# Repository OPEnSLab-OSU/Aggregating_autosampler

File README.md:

# Aggregating_autosampler
Compositing autosampler using weight based sampling targeted for sewage sampling in manholes. Code originally housed in ADS1232 branch of [SingleSampler repository](https://github.com/OPEnSLab-OSU/SingleSampler) and created using [Kawin Pechetratanapanit's sampler framework](https://github.com/OPEnSLab-OSU/OPEnSamplerFramework).

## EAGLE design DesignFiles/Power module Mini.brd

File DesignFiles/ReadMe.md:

[Bill of Materials](https://docs.google.com/spreadsheets/d/12LoKV3FAbf4hfWeB7zsqfaazoJ8oWiLxr8qu5_F6xMY/edit?usp=sharing)

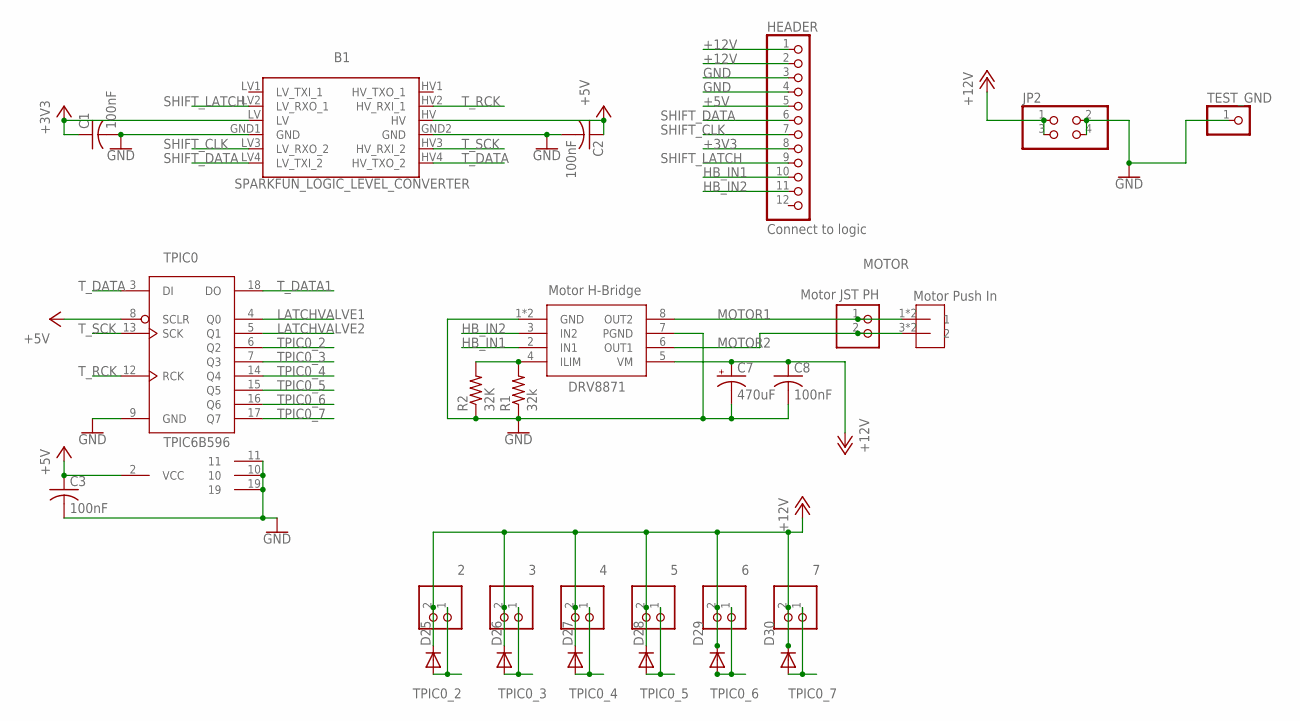
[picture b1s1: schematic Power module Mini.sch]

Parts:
2, 3, 4, 5, 6, 7: 2.5MM_JST_UP_2POS; JST_2POS_2.5MM_UP
B1: SPARKFUN_LOGIC_LEVEL_CONVERTER
C1, C2, C3, C8: 100nF; C1206
C7: 470uF; 140CLH-0810
D25, D26, D27, D28, D29, D30: DIODESOD-123; SOD-123
DRV8871: Motor H-Bridge; SOP8
HEADER: Connect to logic; 1X12
JP2: PINHD-2X2; 2X02
MOTOR: Motor JST PH; JST_2POS_2.5MM_UP
R1: 32k; 0204/5
R2: 32K; R0805
TEST_GND: PINHD-1X1; 1X01
TPIC0: TPIC6B596; DIP20
U$1: Motor Push In; 3.5MM_DIP2

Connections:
+3V3: B1.LV, C1.1, HEADER.8
+5V: B1.HV, C2.1, C3.1, HEADER.5, TPIC0.2 (VCC), TPIC0.8 (SCLR)
+12V: 2.2, 3.2, 4.2, 5.2, 6.2, 7.2, C7.+, C8.1, D25.C, D26.C, D27.C, D28.C, D29.C, D30.C, DRV8871.5 (VM), HEADER.1, HEADER.2, JP2.1, JP2.3
GND: B1.GND1 (GND), B1.GND2 (GND), C1.2, C2.2, C3.2, C7.-, C8.2, DRV8871.1 (GND), DRV8871.7 (PGND), DRV8871.GND, HEADER.3, HEADER.4, JP2.2, JP2.4, R1.1, R2.1, TEST_GND.1, TPIC0.9 (GND), TPIC0.10, TPIC0.11, TPIC0.19
HB_IN1: DRV8871.2 (IN1), HEADER.10
HB_IN2: DRV8871.3 (IN2), HEADER.11
LATCHVALVE1: TPIC0.4 (Q0)
LATCHVALVE2: TPIC0.5 (Q1)
MOTOR1: DRV8871.8 (OUT2), MOTOR.1, U$1.1, U$1.2 (1)
MOTOR2: DRV8871.6 (OUT1), MOTOR.2, U$1.3 (2), U$1.4 (2)
unnamed: DRV8871.4 (ILIM), R1.2, R2.2
SHIFT_CLK: B1.LV3 (LV_RXO_2), HEADER.7
SHIFT_DATA: B1.LV4 (LV_TXI_2), HEADER.6
SHIFT_LATCH: B1.LV2 (LV_RXO_1), HEADER.9
TPIC0_2: 2.1, D25.A, TPIC0.6 (Q2)
TPIC0_3: 3.1, D26.A, TPIC0.7 (Q3)
TPIC0_4: 4.1, D27.A, TPIC0.14 (Q4)
TPIC0_5: 5.1, D28.A, TPIC0.15 (Q5)
TPIC0_6: 6.1, D29.A, TPIC0.16 (Q6)
TPIC0_7: 7.1, D30.A, TPIC0.17 (Q7)
T_DATA: B1.HV4 (HV_TXO_2), TPIC0.3 (DI)
T_DATA1: TPIC0.18 (DO)
T_RCK: B1.HV2 (HV_RXI_1), TPIC0.12 (RCK)
T_SCK: B1.HV3 (HV_RXI_2), TPIC0.13 (SCK)

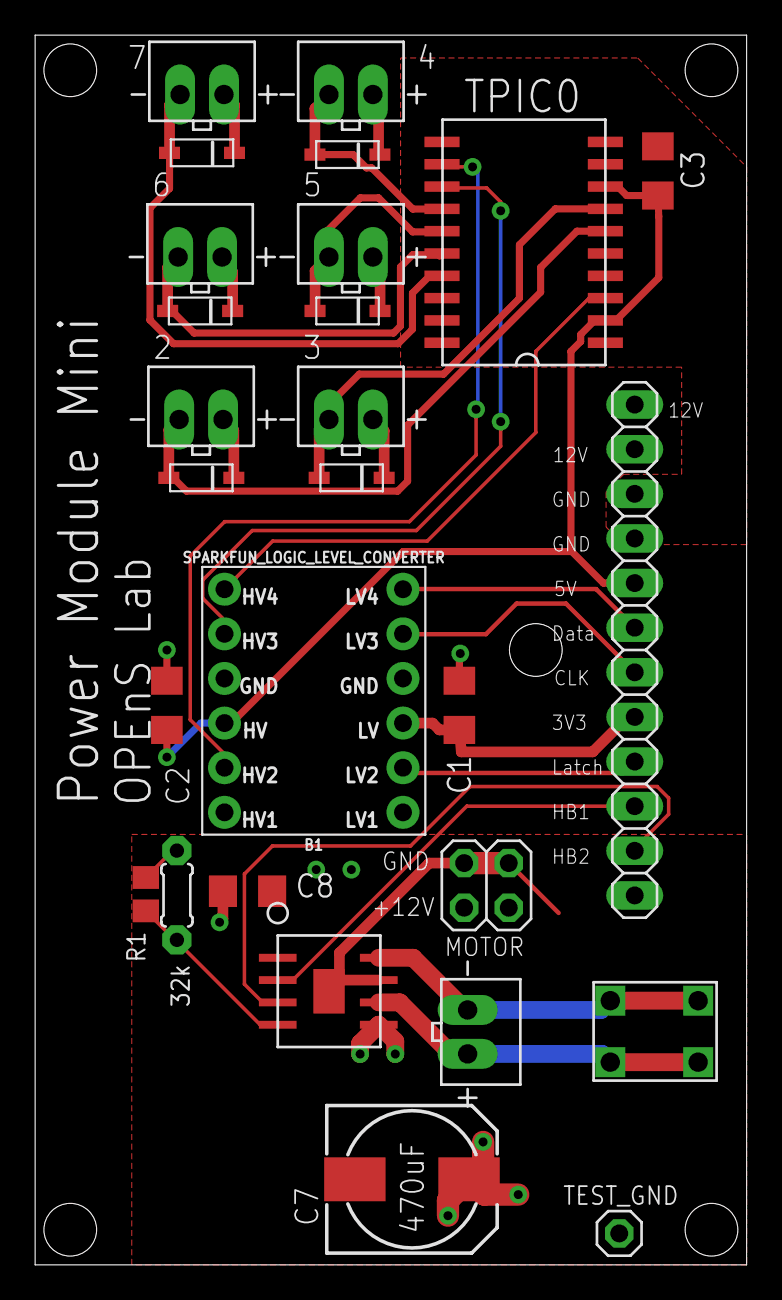
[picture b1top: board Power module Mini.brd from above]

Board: 2 copper layers, 40.5 x 70.0 mm, 27 parts (0 on the bottom side), 21 nets.

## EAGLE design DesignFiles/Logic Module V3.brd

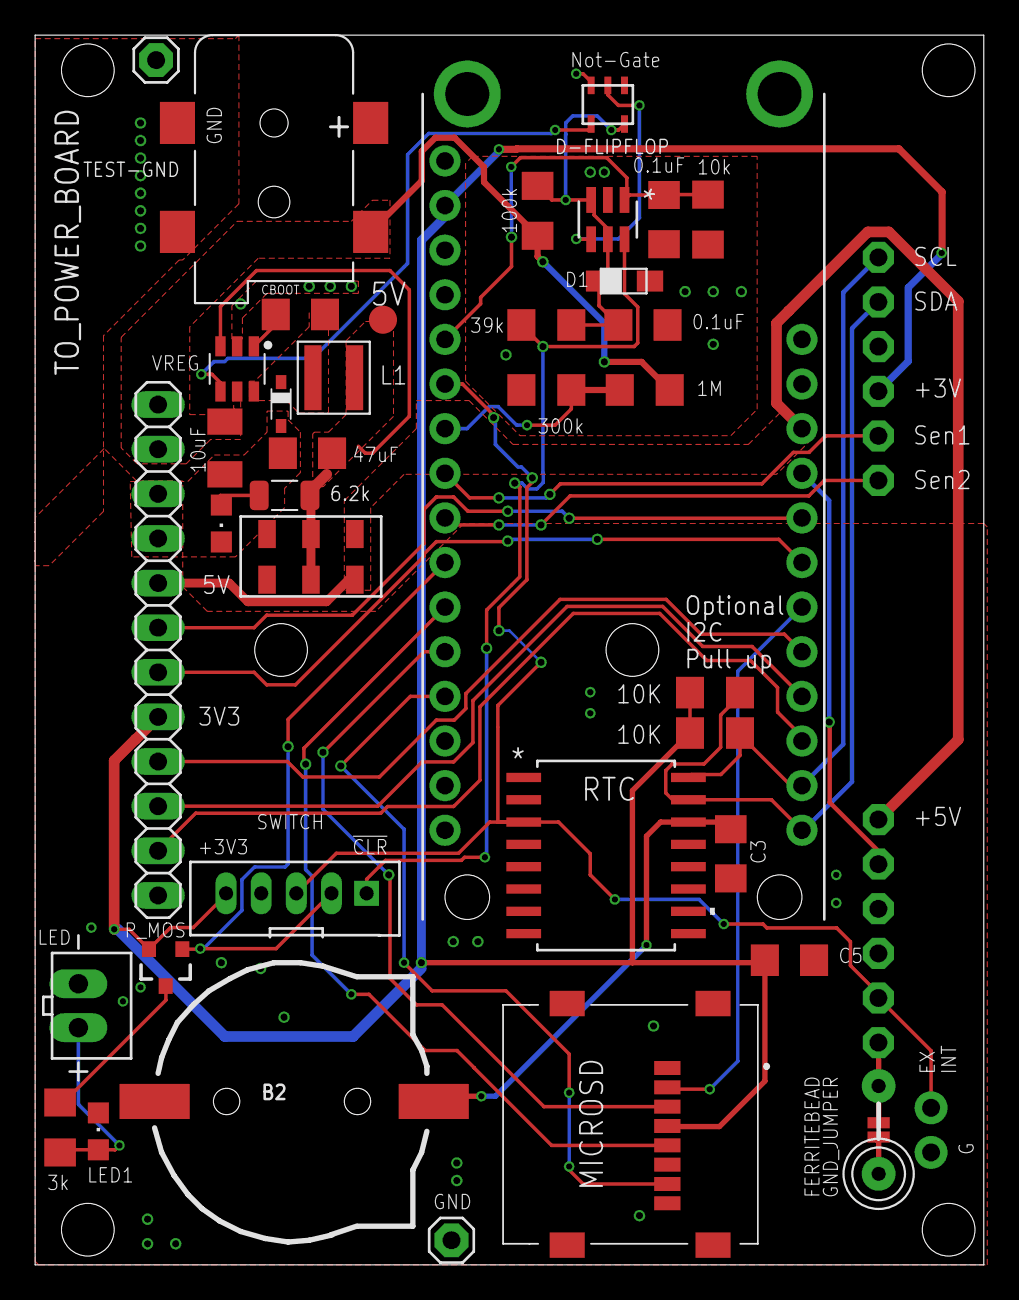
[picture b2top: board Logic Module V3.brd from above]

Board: 2 copper layers, 54.0 x 70.0 mm, 43 parts (1 on the bottom side), 34 nets.

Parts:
5V: TPTP16R; TP16R
12V_IN: 2.1MMJACKSMT; DCJACK_2MM_SMT
B2: cr1220; CR1220-2
C1, C2, C3: 0.1uF; C1206
C5: 100nF; C1206
CBOOT: 100nF; C1206
CIN: 10uF; C1206K
COUT: 47uF; C1206
D1: 4.3V; DO-219AC
D3: NSR0320MW2T1G; SOD323_ST
D-FLIPFLOP: SN74LVC1G175DBVR; DBV6
EXTERNAL_INT: 1X02_NO_SILK
FERRITEBEAD: FB
GND_JUMPER: SMT-JUMPER_2_NO_NO-SILK
L1: 10UH 2.7A; WE-MAPI_40XX
LED: 2.5MM_JST_UP_2POS; JST_2POS_2.5MM_UP
LED1: Yellow; CHIPLED_0805
LED2: RED; CHIPLED_0805
MICROSD: 47219-2001; 472192001
MS1: FEATHERWING
P_MOS: 130mA/20V; SOT23-3
R1: 1M; R1206
R2: 300k; R1206
R3, R5: 10K; R1206
R4: 3k; R1206
R6: 100k; R1206
R7: 39k; R1206
R8: 10k; R1206
R11: 6.2k; RES_1206
RTC: DS3231SNT&R; 21-0042B_16
SWITCH: 2MM_JST_PH_5POS; 2MM_5POS_HEADER
TEST-GND, TEST-GND1: 1X01
TO_POWER_BOARD: 1X12
TO_SENSOR_BOARD1, TO_SENSOR_BOARD2: 1X06-CLEANBIG
U$1: 2PDT_SWITCHJS-SMD; JS-DPDT-SMD
U$2: OPENS-LOGO
U$3: NOT_GATE; SOT753
VREG: BUCK_REGULATORS; SOT23-6

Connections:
2.2VCC: C1.1, D1.FNT, D-FLIPFLOP.3, D-FLIPFLOP.5, R6.1, R7.2, U$3.5
5VUSB: 5V.TP, COUT.1, L1.2, R11.2, U$1.P$2, U$1.P$5, VREG.3
!CLR: D-FLIPFLOP.6, R7.1, SWITCH.1
!EN: D-FLIPFLOP.4, U$3.2
+3V3: C5.1, MICROSD.4, MS1.2, P_MOS.2, R3.2, R5.2, SWITCH.5, TO_POWER_BOARD.8, TO_SENSOR_BOARD1.4
+5V: MS1.26, TO_POWER_BOARD.5, TO_SENSOR_BOARD2.1, U$1.P$1, U$1.P$4
+12V: 12V_IN.PWR2, CIN.1, R1.2, R6.2, TO_POWER_BOARD.1, TO_POWER_BOARD.2, VREG.5
BATTERY_READ: MS1.7, R1.1, R2.2
BUTTON1: MS1.25, TO_SENSOR_BOARD2.2
CS: MICROSD.2, MS1.22
DI: MICROSD.3, MS1.12
DO: MICROSD.7, MS1.13
EN: U$3.4, VREG.4
GND: 12V_IN.GND, 12V_IN.GNDBREAK, B2.-, C1.2, C2.1, C3.2, C5.2, CIN.2, COUT.2, D1.BCK, D3.A, D-FLIPFLOP.2, EXTERNAL_INT.1, FERRITEBEAD.P$2, GND_JUMPER.1, LED.1, LED1.C, LED2.C, MICROSD.6, MICROSD.9, MICROSD.10, MICROSD.11, MICROSD.12, MS1.4, R2.1, R8.1, RTC.2, RTC.5, RTC.6, RTC.7, RTC.8, RTC.9, RTC.10, RTC.11, RTC.12, RTC.13, SWITCH.4, TEST-GND.1, TEST-GND1.1, TO_POWER_BOARD.3, TO_POWER_BOARD.4, U$3.3, VREG.2
HB_IN1: MS1.20, TO_POWER_BOARD.10
HB_IN2: MS1.19, TO_POWER_BOARD.11
unnamed: B2.+, C3.1, RTC.14
unnamed: P_MOS.3, R4.2
unnamed: LED.2, LED1.A, R4.1
unnamed: FERRITEBEAD.P$1, GND_JUMPER.2, TO_SENSOR_BOARD2.6
unnamed: LED2.A, R11.1
unnamed: CBOOT.1, VREG.1
unnamed: CBOOT.2, D3.C, L1.1, VREG.6
RTC_INT: EXTERNAL_INT.2, MS1.6, RTC.3, SWITCH.3, TO_SENSOR_BOARD2.5
SCK: MICROSD.5, MS1.11
SCL: MS1.18, R3.1, RTC.16, TO_SENSOR_BOARD1.1
SDA: MS1.17, R5.1, RTC.15, TO_SENSOR_BOARD1.2
SENSOR1: MS1.8, TO_SENSOR_BOARD1.5
SENSOR2: MS1.9, TO_SENSOR_BOARD1.6
SHIFT_CLK: MS1.23, TO_POWER_BOARD.7
SHIFT_DATA: MS1.24, TO_POWER_BOARD.6
SHIFT_LATCH: MS1.21, TO_POWER_BOARD.9
SHUTDOWN: C2.2, D-FLIPFLOP.1, MS1.5, R8.2
WAKE_NOSLEEP: MS1.10, P_MOS.1, SWITCH.2

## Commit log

2022-08-15 Formatted for publication
    Added read me and put in folders
2022-08-16 Added pressure print at end of cycle
    re-arranged other prints to have cycle number last
2022-08-16 Fixed pressure print message
2022-08-16 Align with master branch
2022-08-16 Weight offset changed for sampler 1
2022-08-16 Reordered states and added comments for clarity
2022-08-16 Wt_offset option for different samplers
2022-08-16 Re-ordered states for clarity
2022-08-16 Added FILL_TIME as variable
2022-08-16 switched to sampler2 code variant
2022-12-19 fixed link
2022-12-19 Fixed spelling
2022-12-19 trimmed
2022-12-20 Added enclosure drawings

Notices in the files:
parts and their libraries:
SparkFun-Jumpers: Licensing: Creative Commons ShareAlike 4.0 International - https://creativecommons.org/licenses/by-sa/4.0
EMCComponents: Copyright: Würth Elektronik
